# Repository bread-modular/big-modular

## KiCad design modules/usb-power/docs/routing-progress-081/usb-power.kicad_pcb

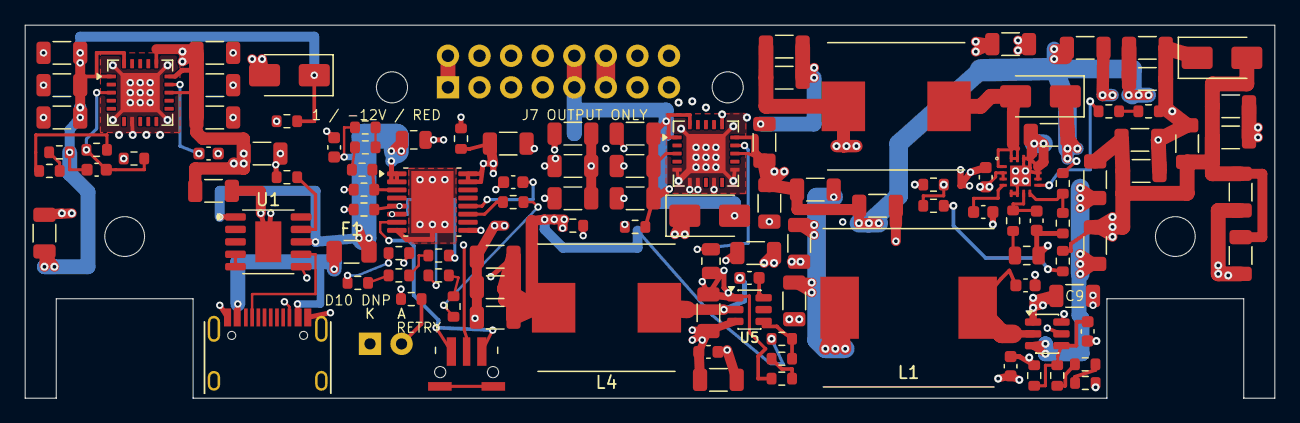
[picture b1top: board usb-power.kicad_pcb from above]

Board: 4 copper layers, 100.5 x 30.0 mm, 116 parts (0 on the bottom side), 50 nets.

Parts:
C1, C60, C86: 1u 50V X7R; C_0805_2012Metric
C2, C3, C7, C20, C35, C36, C61, C85, C88: 100n 50V X7R; C_0603_1608Metric
C4: 10u 50V X5R; C_1206_3216Metric
C5, C6, C9, C18, C19, C37, C38, C48, C49, C50, C51, C52, C53, C54, C55, C56, C57, C58, C59, C63, C64, C65, C66, C67, C68, C69, C70, C71, C72, C73, C74, C75, C76, C77, C78, C79, C80, C82, C83, C84: 22u 25V X5R; C_1206_3216Metric
C62: 10n 50V X7R; C_0603_1608Metric
C87: 100p 50V C0G; C_0603_1608Metric
C89, C90, C91, C92: 2.2u 50V X7R; C_1206_3216Metric
C93: DNP CFF / TBD; C_0603_1608Metric
D10: RED 3mm / +5V POWER / DNP; LED_D3.0mm_Horizontal_O1.27mm_Z2.0mm_Edge
D27, D28, D29, D30: SS34 40V; D_SMA
F1: 3A 32V candidate; Fuse_1206_3216Metric
J1: TYPE-C-31-M-12; HRO-TYPE-C-31-M-12
J7: Manual IDC wire landing; WireLanding_2x08_P2.54mm
L1: 22uH 20% shielded; L_TMPC1205HP_220M
L4, L5: 6.8uH 20% shielded; L_SLO1040H6R8MTT
R2: 6.8k 1%; R_0603_1608Metric
R4: 470k 1%; R_0603_1608Metric
R5, R7, R17, R81, R88, R91: 100k 1%; R_0603_1608Metric
R6: 806k 1%; R_0603_1608Metric
R8: 5.6k 1%; R_0603_1608Metric
R9, R86: 100k 0.1%; R_0603_1608Metric
R10, R74, R87: 10k 0.1%; R_0603_1608Metric
R15: 120k 0.1%; R_0603_1608Metric
R18: 13k 1%; R_0603_1608Metric
R25, R26, R27, R31, R78: 10k 1%; R_0603_1608Metric
R32: 1k 1%; R_0603_1608Metric
R36: 300k 1%; R_0603_1608Metric
R72: 90.9k 0.1%; R_0603_1608Metric
R73: 1.2k 1%; R_0603_1608Metric
R77: 82k 1%; R_0603_1608Metric
R79, R80: 220 1%; R_0603_1608Metric
R82, R93: 2k 1%; R_0603_1608Metric
R83: 0 1%; R_0603_1608Metric
R84: 6.2k 1%; R_0603_1608Metric
R85: 510 1%; R_0603_1608Metric
R89: 470 1%; R_0603_1608Metric
R90, R92: 20k 1%; R_0603_1608Metric
SW1: TL3340AF160QG; SW_TL3340AF160QG_HandSolder
U1: CH224A; SSOP-10-1EP_3.9x4.9mm_P1mm_EP2.1x3.3mm
U2: TPS26600PWPR; HTSSOP-16-1EP_4.4x5mm_P0.65mm_EP3.4x5mm_Mask2.66x2.46mm
U3, U5: TPS54302DDCR; SOT-23-6
U12: TPS7A4700RGWR; Texas_RGW0020A_VQFN-20-1EP_5x5mm_P0.65mm_EP3.15x3.15mm
U13: TPS7A3301RGWR; Texas_RGW0020A_VQFN-20-1EP_5x5mm_P0.65mm_EP3.15x3.15mm
U14: TPS55340RTER; Texas_RTE0016C_WQFN-16-1EP_3x3mm_P0.5mm_EP1.68x1.68mm

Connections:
/Autonomous hardware window and retry/EF_MODE: R36.1, U2.6 (MODE)
/Autonomous hardware window and retry/EF_SHDN: SW1.1 (COMMON), SW1.3 (COMMON), U2.7 (SHDN)
/Autonomous hardware window and retry/ILIM: R8.1, U2.11 (ILIM)
/Autonomous hardware window and retry/ILIM_SER_1: R8.2, R79.1
/Autonomous hardware window and retry/ILIM_SER_2: R79.2, R80.1
/Autonomous hardware window and retry/MODE_SER_1: R36.2, R81.1
/Autonomous hardware window and retry/MODE_SER_2: R81.2, R82.1
/Autonomous hardware window and retry/OV_SET: R6.2, R7.1, U2.5 (OVP)
/Autonomous hardware window and retry/RTN: C3.2, R5.2, R7.2, R80.2, R82.2, SW1.2 (NO), U2.8 (RTN), U2.17 (EP_RTN)
/Autonomous hardware window and retry/SLEW: C3.1, U2.12 (dVdT)
/Autonomous hardware window and retry/UV_EN: R5.1, R78.2, U2.3 (UVLO)
/Autonomous hardware window and retry/UV_SER_1: R4.2, R77.1
/Autonomous hardware window and retry/UV_SER_2: R77.2, R78.1
/Board output and power LED/LED_P_A: D10.2 (A), R32.2
/Direct 9V negative IBB/NINV_BOOT: C35.1, U3.6 (BOOT)
/Direct 9V negative IBB/NINV_DIV1: R9.2, R15.1
/Direct 9V negative IBB/NINV_DIV2: R15.2, R84.1
/Direct 9V negative IBB/NINV_EN: R91.2, R92.1, U3.5 (EN)
/Direct 9V negative IBB/NINV_EN_LO: R92.2, R93.1
/Direct 9V negative IBB/NINV_FB: C93.2, R10.1, R84.2, U3.4 (FB)
/Direct 9V negative IBB/NINV_SW: C35.2, L1.1, U3.2 (SW)
/Direct 9V negative IBB/NRAW: C6.1, C7.2, C9.1, C37.1, C54.1, C55.1, C56.1, C67.1, C70.1, C71.1, C74.1, C75.1, C76.1, C89.2, C90.2, C91.2, C92.2, D28.2 (A), D30.2 (A), R10.2, R93.2, U3.1 (GND), U13.13 (EN), U13.15 (IN), U13.16 (IN)
/Direct 9V positive boost/PBOOST_COMP: C87.1, R89.1, U14.7 (COMP)
/Direct 9V positive boost/PBOOST_COMP_RC: C86.1, R89.2
/Direct 9V positive boost/PBOOST_FB: R86.2, R87.1, U14.8 (FB)
/Direct 9V positive boost/PBOOST_FREQ: R88.1, U14.9 (FREQ)
/Direct 9V positive boost/PBOOST_FREQ_SER: R88.2, R90.1
/Direct 9V positive boost/PBOOST_SS: C85.1, U14.4 (SS)
/Direct 9V positive boost/PBOOST_SW: D29.2 (A), L5.2, U14.1 (SW), U14.15 (SW), U14.16 (SW)
/Direct 9V positive boost/PRAW: C48.1, C49.1, C50.1, C63.1, C77.1, C78.1, C79.1, C80.1, D27.1 (K), D29.1 (K), R86.1, U12.13 (EN), U12.15 (IN), U12.16 (IN)
/GND: C1.2, C2.2, C4.2, C5.2, C6.2, C9.2, C18.2, C19.2, C20.2, C37.2, C38.2, C48.2, C49.2, C50.2, C51.2, C52.2, C53.2, C54.2, C55.2, C56.2, C57.2, C58.2, C59.2, C60.2, C61.2, C63.2, C64.2, C65.2, C66.2, C67.2, C68.2, C69.2, C70.2, C71.2, C72.2, C73.2, C74.2, C75.2, C76.2, C77.2, C78.2, C79.2, C80.2, C82.2, C83.2, C84.2, C85.2, C86.2, C87.2, C88.2, C93.1, D10.1 (K), D30.1 (K), J1.A1 (GND), J1.A12 (GND), J1.S1 (SHIELD), J7.3, J7.4, J7.5, J7.6, J7.7, J7.8, L1.2, R2.2, R9.1, R25.2, R26.2, R27.2, R31.2, R74.2, R85.2, R87.2, R90.2, U1.11 (EP0_GND), U2.9 (GND), U5.1 (GND), U12.5 (6P4V1), U12.6 (3P2V), U12.7 (GND), U12.9 (0P8V), U12.11 (0P2V), U12.21 (EP_GND), U13.7 (GND), U13.21 (EP_GND), U14.5 (SYNC), U14.6 (AGND), U14.10 (RSVD_GND), U14.11 (PGND), U14.12 (PGND), U14.13 (PGND), U14.14 (RSVD_GND), U14.17 (EP_AGND)
/Independent +5V buck/FIVE_BOOT: C36.1, U5.6 (BOOT)
/Independent +5V buck/FIVE_DIV_LO: R18.2, R85.1
/Independent +5V buck/FIVE_FB: R17.2, R18.1, U5.4 (FB)
/Independent +5V buck/FIVE_SW: C36.2, L4.1, U5.2 (SW)
/N12: C57.1, C58.1, C59.1, C62.1, C73.1, D28.1 (K), J7.1, J7.2, R26.1, R72.1, U13.1 (OUT), U13.20 (OUT)
/P5: C19.1, C38.1, C72.1, J7.11, J7.12, L4.2, R17.1, R27.1, R32.1
/P12: C51.1, C52.1, C53.1, C64.1, C65.1, C66.1, D27.2 (A), J7.9, J7.10, R25.1, U12.1 (OUT), U12.3 (SENSE), U12.20 (OUT)
/Quiet bipolar post-regulators/N_LDO_DIV: R73.1, R83.2
/Quiet bipolar post-regulators/N_LDO_FB: C62.2, R73.2, R74.1, U13.3 (FB)
/Quiet bipolar post-regulators/N_LDO_SER: R72.2, R83.1
/Quiet bipolar post-regulators/N_NR: C61.1, U13.14 (NR/SS)
/Quiet bipolar post-regulators/P_NR: C60.1, U12.14 (NR)
/USB PD input/CC1: J1.A5 (CC1), U1.7 (CC1)
/USB PD input/CC2: J1.B5 (CC2), U1.6 (CC2)
/USB PD input/PD_CFG: R2.1, U1.9 (CFG1)
/USB PD input/PD_D_SHORT: U1.4 (DP), U1.5 (DM)
/USB PD input/USB_VBUS: F1.1, J1.A4 (VBUS), J1.A9 (VBUS)
/VIN9: C1.1, C2.1, F1.2, R4.1, R6.1, U1.1 (VHV), U1.8 (VBUS_SENSE), U2.1 (IN), U2.2 (IN)
/VPROT: C4.1, C5.1, C7.1, C18.1, C20.1, C68.1, C69.1, C82.1, C83.1, C84.1, C88.1, C89.1, C90.1, C91.1, C92.1, L5.1, R31.1, R91.1, U2.15 (OUT), U2.16 (OUT), U3.3 (VIN), U5.3 (VIN), U14.2 (VIN), U14.3 (EN)

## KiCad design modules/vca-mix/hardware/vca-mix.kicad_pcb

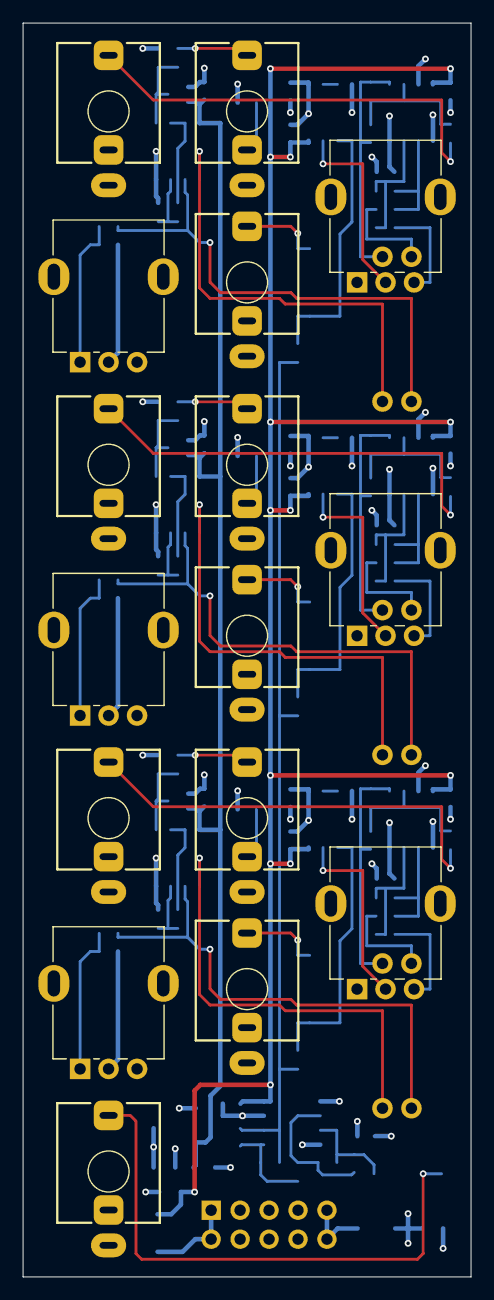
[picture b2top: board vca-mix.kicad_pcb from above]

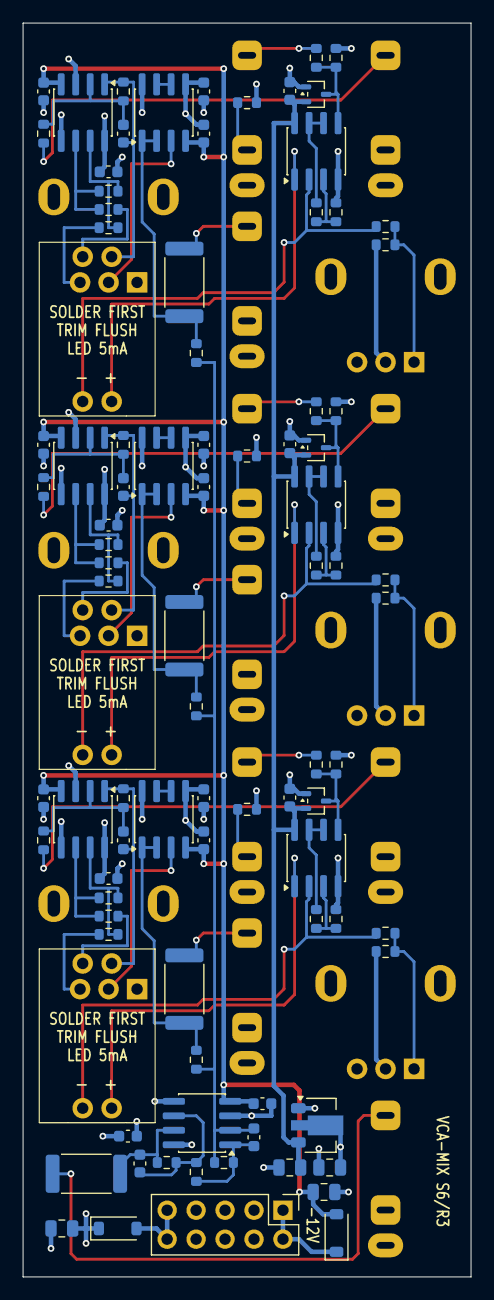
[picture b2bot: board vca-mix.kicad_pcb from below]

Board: 4 copper layers, 39.3 x 110.0 mm, 108 parts (92 on the bottom side), 68 nets.

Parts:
C101, C201, C301, C401, C402: 20p; C_0603_1608Metric
C103, C104, C105, C107, C108, C203, C204, C205, C207, C208, C303, C304, C305, C307, C308, C403, C404: 100n; C_0603_1608Metric
C501, C502, C504: 10u; C_0805_2012Metric
C503: 1u; C_0805_2012Metric
D101, D201, D301: BAT54SW; SOT-323_SC-70
D501, D502: B5819W; D_SOD-123
J1, J2, J3, J4, J5, J6, J7, J8, J9, J11: PJ301M-12; Jack_3.5mm_QingPu_WQP-PJ301M-12_Vertical
J10: Eurorack_2x5; PinHeader_2x05_P2.54mm_Vertical
R101, R102, R106, R111, R201, R202, R206, R211, R301, R302, R306, R311, R401, R402, R403: 100k; R_0603_1608Metric
R103, R104, R114, R203, R204, R214, R303, R304, R314: 10k; R_0603_1608Metric
R105, R205, R305, R404: 1k; R_2512_6332Metric
R107, R207, R307: 200k; R_0603_1608Metric
R108, R208, R308: 51k; R_0603_1608Metric
R109, R209, R309: 330; R_0603_1608Metric
R110, R210, R310: 100; R_0603_1608Metric
R112, R113, R212, R213, R312, R313: 1M; R_0603_1608Metric
RV1, RV2, RV3, RV4, RV5, RV6: 50k; Potentiometer_RV09
U101, U103, U201, U203, U301, U303, U401: TL072CDT; SOIC-8_3.9x4.9mm_P1.27mm
U102, U202, U302: MCP6002; SOIC-8_3.9x4.9mm_P1.27mm
U104, U204, U304: VTL5C
U501: HT7533-1; SOT-89-3

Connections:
+3V3: C105.1, C205.1, C305.1, C504.1, D101.2, D201.2, D301.2, U102.8, U202.8, U302.8, U501.3
+12V: C103.1, C107.1, C203.1, C207.1, C303.1, C307.1, C403.1, C501.1, C503.1, D501.1, R107.1, R207.1, R307.1, U101.8, U103.8, U201.8, U203.8, U301.8, U303.8, U401.8, U501.2
-12V: C104.2, C108.2, C204.2, C208.2, C304.2, C308.2, C404.2, C502.2, D502.2, U101.4, U103.4, U201.4, U203.4, U301.4, U303.4, U401.4
/+12V_IN: D501.2, J10.9, J10.10
/-12V_IN: D502.1, J10.1, J10.2
/BUF1: C101.2, R102.2, U101.1, U104.4
/BUF2: C201.2, R202.2, U201.1, U204.4
/BUF3: C301.2, R302.2, U301.1, U304.4
/CHO1: R105.1, R111.1, U103.1, U103.2
/CHO2: R205.1, R211.1, U203.1, U203.2
/CHO3: R305.1, R311.1, U303.1, U303.2
/CV1: J2.T, R108.1
/CV2: J5.T, R208.1
/CV3: J8.T, R308.1
/CVB1: R112.1, U102.6, U102.7
/CVB2: R212.1, U202.6, U202.7
/CVB3: R312.1, U302.6, U302.7
/CVD1: D101.3, R106.1, R108.2, U102.5
/CVD2: D201.3, R206.1, R208.2, U202.5
/CVD3: D301.3, R306.1, R308.2, U302.5
/CVH1: R112.2, R113.1, U102.3
/CVH2: R212.2, R213.1, U202.3
/CVH3: R312.2, R313.1, U302.3
/CVN1: J2.TN, R107.2
/CVN2: J5.TN, R207.2
/CVN3: J8.TN, R307.2
/IN1: J1.T, R101.1
/IN2: J4.T, R201.1
/IN3: J7.T, R301.1
/INV1: C101.1, R101.2, R102.1, U101.2
/INV2: C201.1, R201.2, R202.1, U201.2
/INV3: C301.1, R301.2, R302.1, U301.2
/LDR1: R103.1, U104.3
/LDR2: R203.1, U204.3
/LDR3: R303.1, U304.3
/MINV: C402.1, R402.2, R403.1, U401.6
/MIX: J11.T, R404.2
/MIXO: C402.2, R403.2, R404.1, U401.7
/OUT1: J3.T, R105.2
/OUT2: J6.T, R205.2
/OUT3: J9.T, R305.2
/RNG1: R109.2, R114.1, RV4.1
/RNG2: R209.2, R214.1, RV5.1
/RNG3: R309.2, R314.1, RV6.1
/SPARE1: U103.6, U103.7
/SPARE2: U203.6, U203.7
/SPARE3: U303.6, U303.7
/SUM: C401.1, R111.2, R211.2, R311.2, R401.1, U401.2
/SUMO: C401.2, R401.2, R402.1, U401.1
/VACN1: R109.1, U102.2, U104.1
/VACN2: R209.1, U202.2, U204.1
/VACN3: R309.1, U302.2, U304.1
/VACP1: U102.1, U104.2
/VACP2: U202.1, U204.2
/VACP3: U302.1, U304.2
/VCA1: R104.2, R110.1, U101.7
/VCA2: R204.2, R210.1, U201.7
/VCA3: R304.2, R310.1, U301.7
/VOLT1: R110.2, RV1.3
/VOLT2: R210.2, RV2.3
/VOLT3: R310.2, RV3.3
/VOLW1: RV1.2, U103.3
/VOLW2: RV2.2, U203.3
/VOLW3: RV3.2, U303.3
/VSUM1: R103.2, R104.1, U101.6
/VSUM2: R203.2, R204.1, U201.6
/VSUM3: R303.2, R304.1, U301.6
GND: C103.2, C104.1, C105.2, C107.2, C108.1, C203.2, C204.1, C205.2, C207.2, C208.1, C303.2, C304.1, C305.2, C307.2, C308.1, C403.2, C404.1, C501.2, C502.1, C503.2, C504.2, D101.1, D201.1, D301.1, J1.S, J1.TN, J2.S, J3.S, J4.S, J4.TN, J5.S, J6.S, J7.S, J7.TN, J8.S, J9.S, J10.3, J10.4, J10.5, J10.6, J10.7, J10.8, J11.S, R106.2, R113.2, R114.2, R206.2, R213.2, R214.2, R306.2, R313.2, R314.2, RV1.1, RV2.1, RV3.1, RV4.2, RV4.3, RV5.2, RV5.3, RV6.2, RV6.3, U101.3, U101.5, U102.4, U103.5, U201.3, U201.5, U202.4, U203.5, U301.3, U301.5, U302.4, U303.5, U401.3, U401.5, U501.1

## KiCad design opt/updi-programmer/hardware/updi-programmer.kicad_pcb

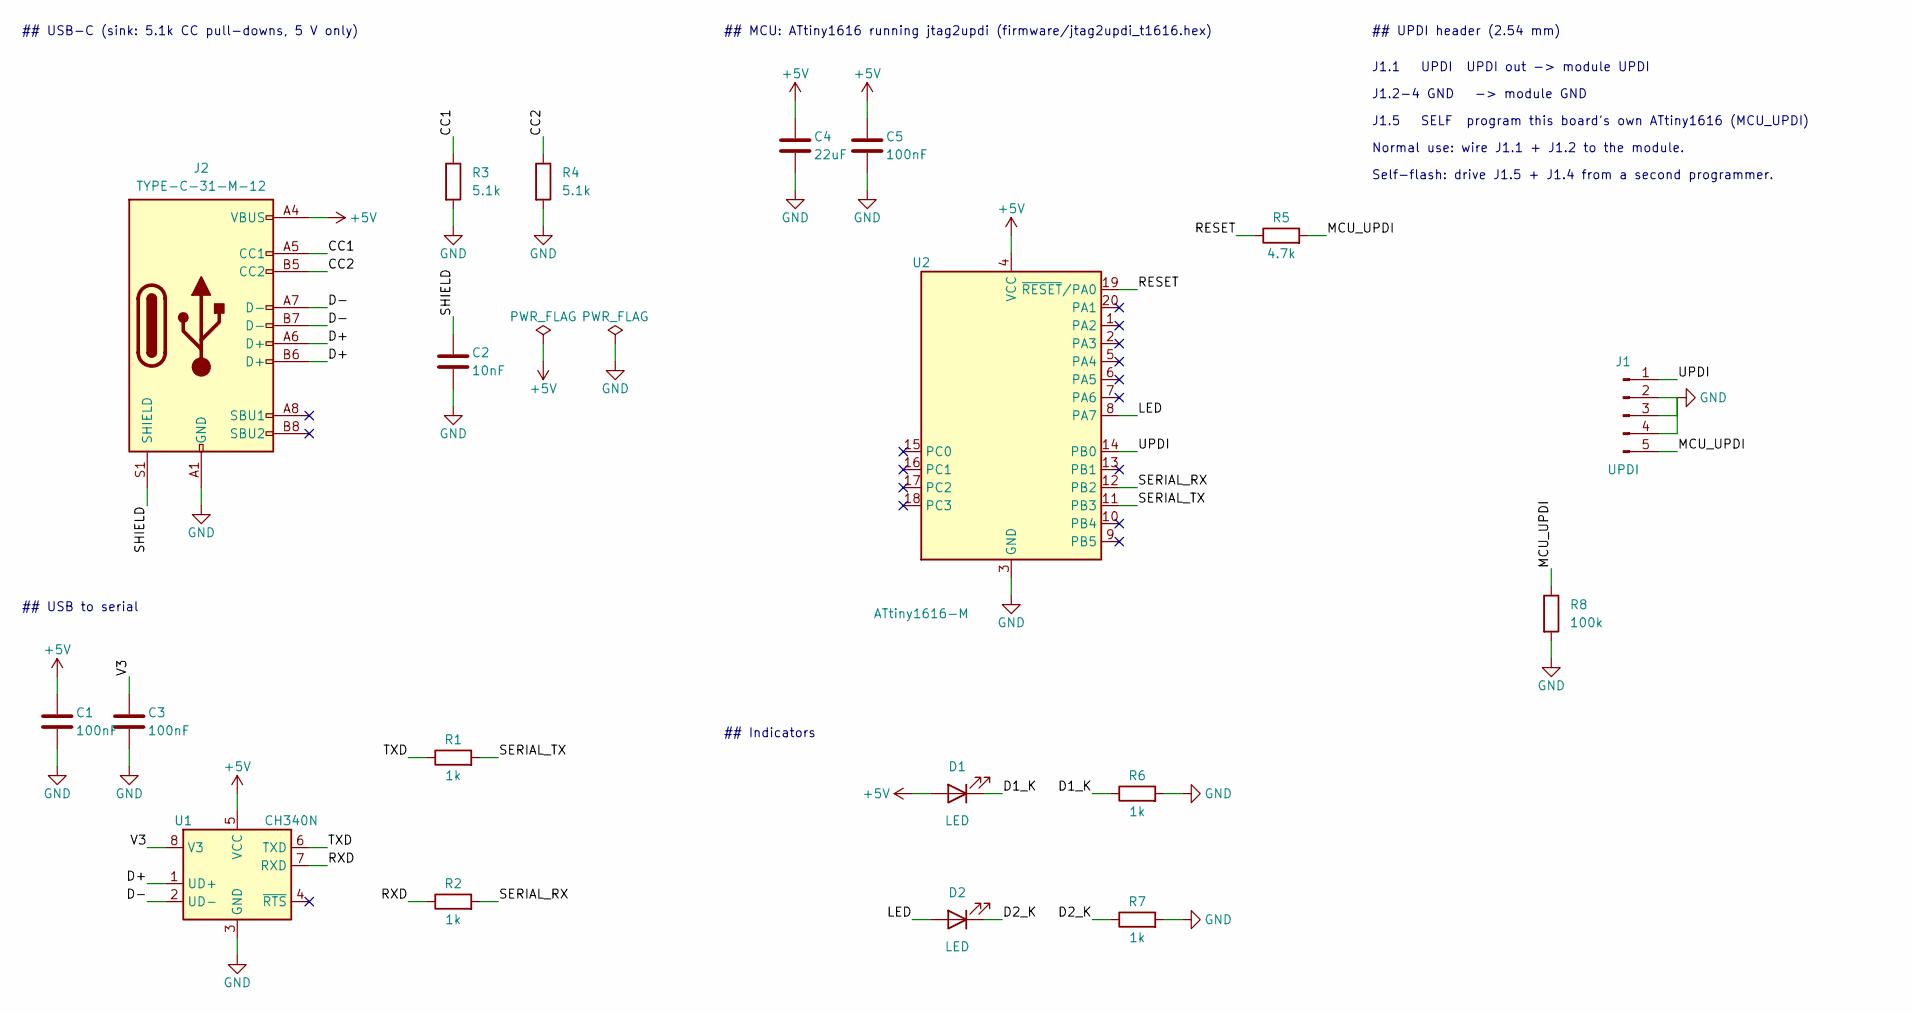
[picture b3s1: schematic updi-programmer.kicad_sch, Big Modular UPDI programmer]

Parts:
C1, C3, C5: 100nF; C_0402_1005Metric; MPN CL05B104KO5NNNC; LCSC C1525
C2: 10nF; C_0805_2012Metric; MPN CL21B103KBANNNC; LCSC C1710
C4: 22uF; C_1206_3216Metric; MPN CL31A226KAHNNNE; LCSC C12891
D1: LED; LED_0603_1608Metric; MPN KT-0603R; LCSC C2286
D2: LED; LED_0603_1608Metric; MPN KT-0603W; LCSC C2290
J1: UPDI; PinHeader_1x05_P2.54mm_Vertical
J2: TYPE-C-31-M-12; HRO-TYPE-C-31-M-12; MPN TYPE-C-31-M-12; LCSC C165948
R1, R2, R6, R7: 1k; R_0603_1608Metric; MPN 0603WAF1001T5E; LCSC C21190
R3, R4: 5.1k; R_0603_1608Metric; MPN 0603WAF5101T5E; LCSC C23186
R5: 4.7k; R_0603_1608Metric; MPN 0603WAF4701T5E; LCSC C23162
R8: 100k; R_0402_1005Metric; MPN 0402WGF1003TCE; LCSC C25741
U1: CH340N; SOIC-8_3.9x4.9mm_P1.27mm; MPN CH340N; LCSC C2977777
U2: ATtiny1616-M; VQFN-20-1EP_3x3mm_P0.4mm_EP1.7x1.7mm; MPN ATTINY1616-MNR; LCSC C507118

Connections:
+5V: C1.1, C4.1, C5.1, D1.2 (A), J2.A4 (VBUS), J2.A9 (VBUS), U1.5 (VCC), U2.4 (VCC)
/CC1: J2.A5 (CC1), R3.1
/CC2: J2.B5 (CC2), R4.1
/D1_K: D1.1 (K), R6.1
/D2_K: D2.1 (K), R7.1
/D+: J2.A6 (D+), J2.B6 (D+), U1.1 (UD+)
/D-: J2.A7 (D-), J2.B7 (D-), U1.2 (UD-)
/LED: D2.2 (A), U2.8 (PA7)
/MCU_UPDI: J1.5, R5.2, R8.1
/RESET: R5.1, U2.19 (~RESET/PA0)
/RXD: R2.1, U1.7 (RXD)
/SERIAL_RX: R2.2, U2.12 (PB2)
/SERIAL_TX: R1.2, U2.11 (PB3)
/SHIELD: C2.1, J2.S1 (SHIELD)
/TXD: R1.1, U1.6 (TXD)
/UPDI: J1.1, U2.14 (PB0)
/V3: C3.1, U1.8 (V3)
GND: C1.2, C2.2, C3.2, C4.2, C5.2, J1.2, J1.3, J1.4, J2.A1 (GND), J2.A12 (GND), R3.2, R4.2, R6.2, R7.2, R8.2, U1.3 (GND), U2.3 (GND), U2.21 (GND)

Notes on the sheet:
## USB-C (sink: 5.1k CC pull-downs, 5 V only)
## USB to serial
## MCU: ATtiny1616 running jtag2updi (firmware/jtag2updi_t1616.hex)
## Indicators
## UPDI header (2.54 mm)
J1.1 UPDI UPDI out -> module UPDI
J1.2-4 GND -> module GND
J1.5 SELF program this board's own ATtiny1616 (MCU_UPDI)
Normal use: wire J1.1 + J1.2 to the module.
Self-flash: drive J1.5 + J1.4 from a second programmer.

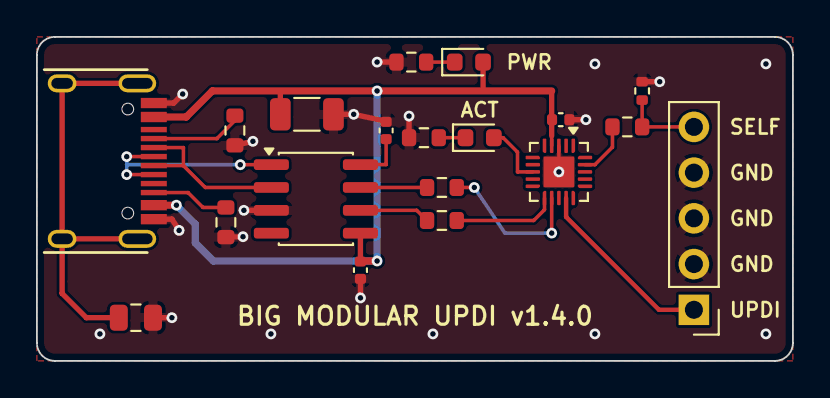
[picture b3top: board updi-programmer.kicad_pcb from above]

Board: 2 copper layers, 42.0 x 18.0 mm, 19 parts (0 on the bottom side), 18 nets.
